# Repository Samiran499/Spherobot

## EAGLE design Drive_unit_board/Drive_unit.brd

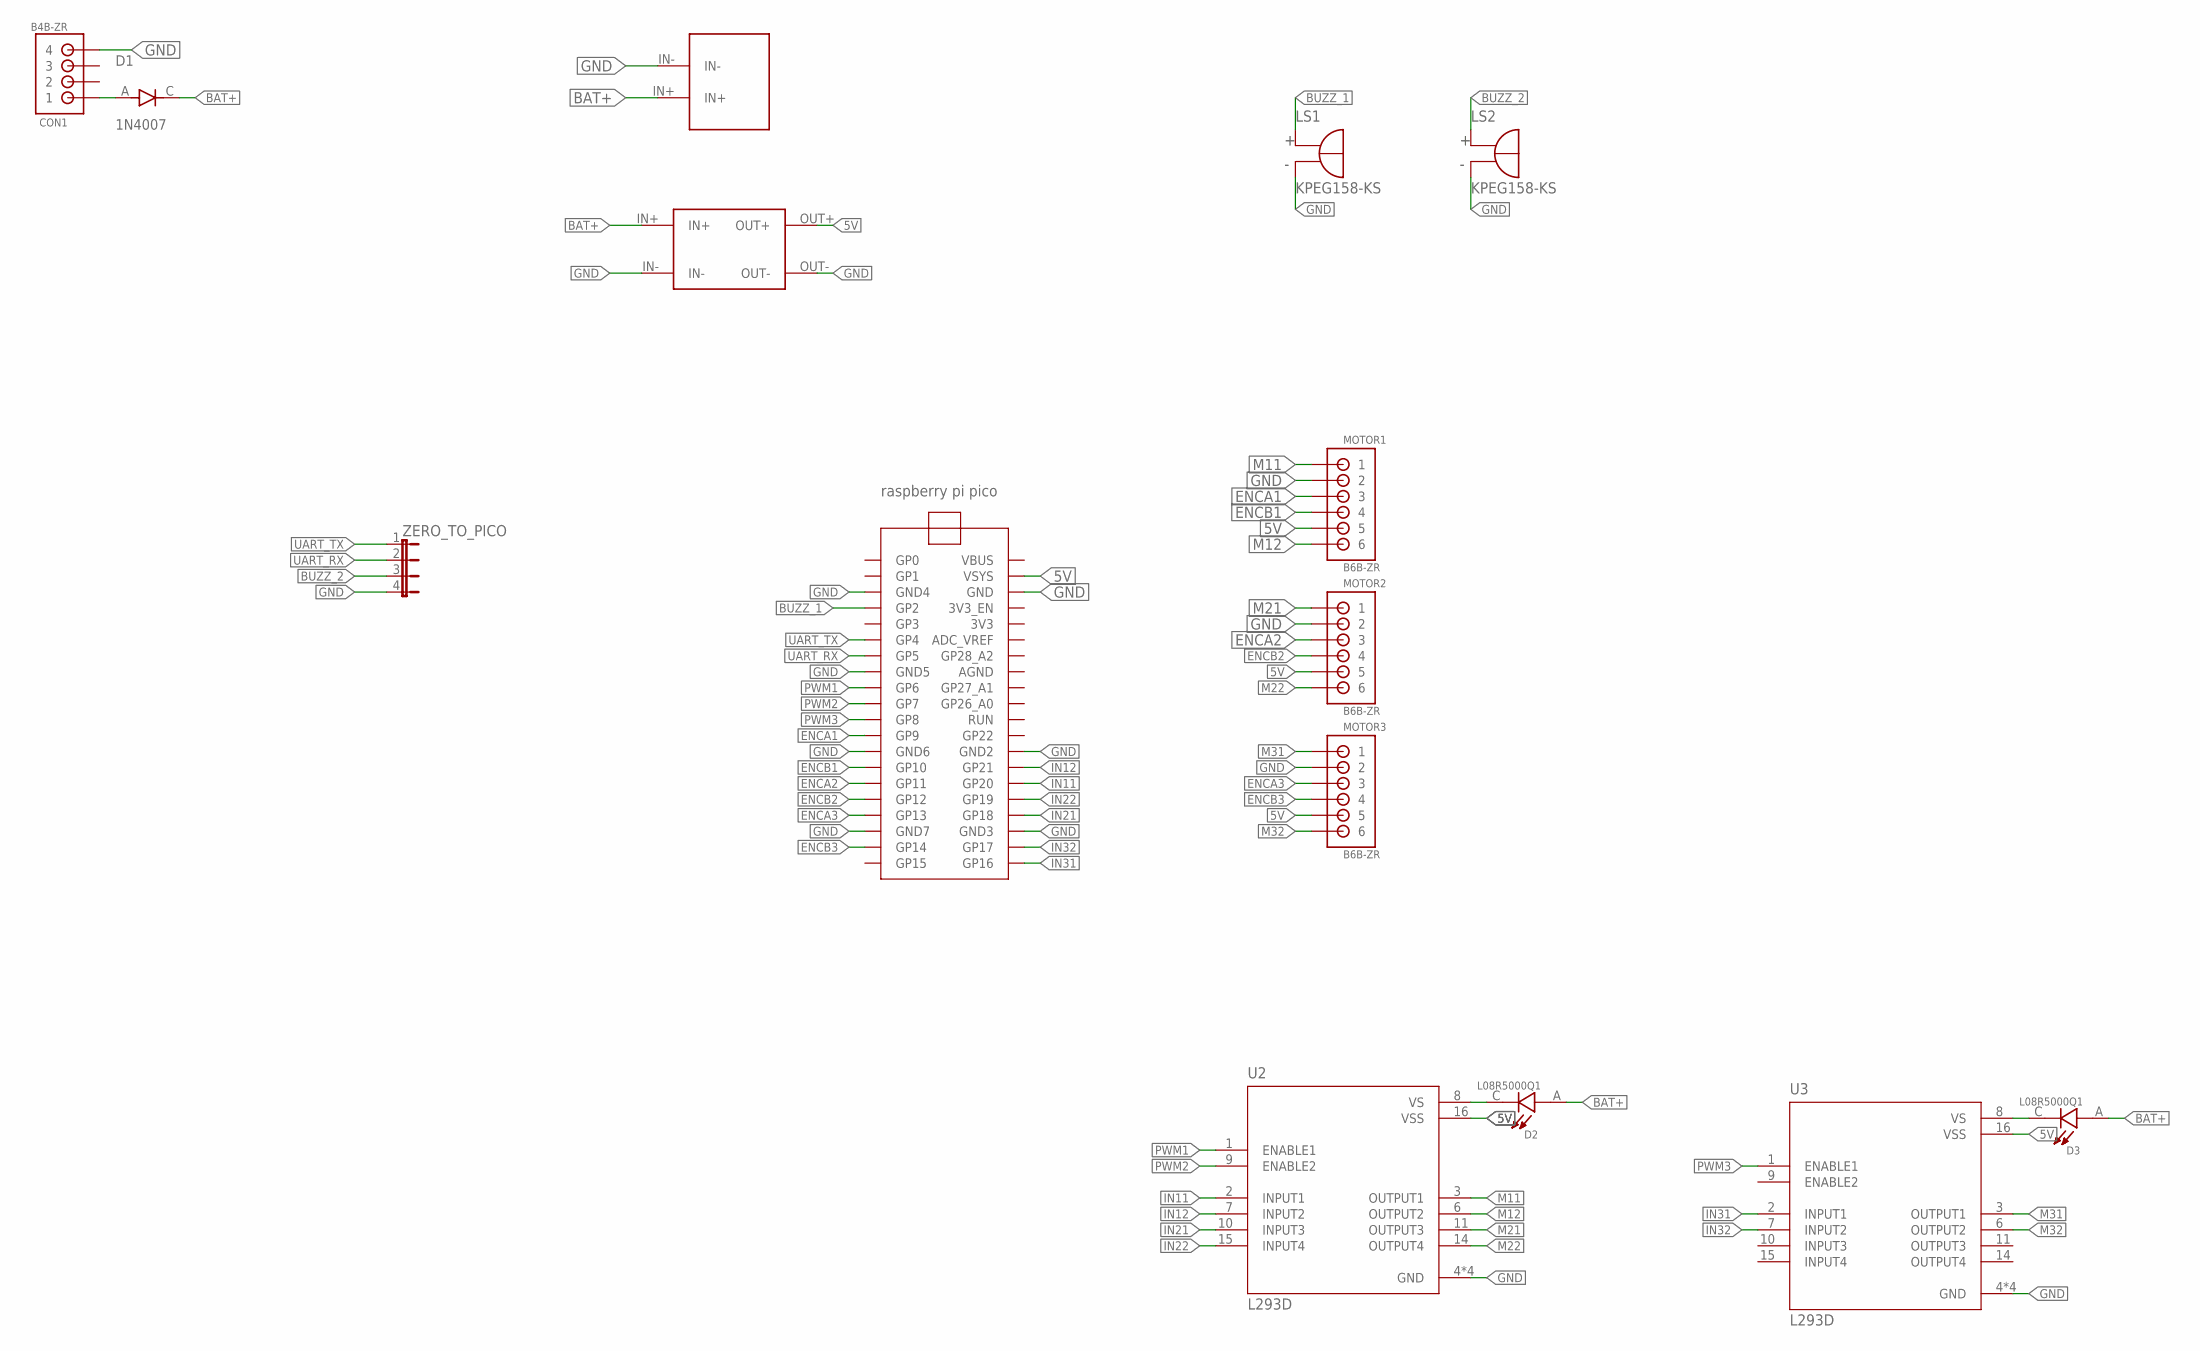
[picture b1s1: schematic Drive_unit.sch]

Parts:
CON1: B4B-ZR
D1: 1N4007; DIOAD1060W80L520D270
D2, D3: L08R5000Q1; LEDRD254W57D500H1070
LS1, LS2: KPEG158-KS; XDCR_KPEG158-KS
MOTOR1, MOTOR2, MOTOR3: B6B-ZR
U1: RASPBERRY_PI_PICO
U2, U3: L293D; DIP880W50P254L2000H510Q16
U$1: USB_BUCK
U$3: LM2596_BUCK_MODULE; LM2596_MODULE
ZERO_TO_PICO: JP4E; JP4

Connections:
5V: MOTOR1.5, MOTOR2.5, MOTOR3.5, U1.VSYS, U2.16 (VSS), U3.16 (VSS), U$3.OUT+
BAT+: D1.C, D2.A, D3.A, U$1.IN+, U$3.IN+
BUZZ_1: LS1.P (POS), U1.GP2
BUZZ_2: LS2.P (POS), ZERO_TO_PICO.3
ENCA1: MOTOR1.3, U1.GP9
ENCA2: MOTOR2.3, U1.GP11
ENCA3: MOTOR3.3, U1.GP13
ENCB1: MOTOR1.4, U1.GP10
ENCB2: MOTOR2.4, U1.GP12
ENCB3: MOTOR3.4, U1.GP14
GND: CON1.4, LS1.N (NEG), LS2.N (NEG), MOTOR1.2, MOTOR2.2, MOTOR3.2, U1.GND, U1.GND2, U1.GND3, U1.GND4, U1.GND5, U1.GND6, U1.GND7, U2.4 (GND), U2.5 (GND), U2.12 (GND), U2.13 (GND), U3.4 (GND), U3.5 (GND), U3.12 (GND), U3.13 (GND), U$1.IN-, U$3.IN-, U$3.OUT-, ZERO_TO_PICO.4
IN11: U1.GP20, U2.2 (INPUT1)
IN12: U1.GP21, U2.7 (INPUT2)
IN21: U1.GP18, U2.10 (INPUT3)
IN22: U1.GP19, U2.15 (INPUT4)
IN31: U1.GP16, U3.2 (INPUT1)
IN32: U1.GP17, U3.7 (INPUT2)
M11: MOTOR1.1, U2.3 (OUTPUT1)
M12: MOTOR1.6, U2.6 (OUTPUT2)
M21: MOTOR2.1, U2.11 (OUTPUT3)
M22: MOTOR2.6, U2.14 (OUTPUT4)
M31: MOTOR3.1, U3.3 (OUTPUT1)
M32: MOTOR3.6, U3.6 (OUTPUT2)
unnamed: CON1.1, D1.A
unnamed: D2.C, U2.8 (VS)
unnamed: D3.C, U3.8 (VS)
PWM1: U1.GP6, U2.1 (ENABLE1)
PWM2: U1.GP7, U2.9 (ENABLE2)
PWM3: U1.GP8, U3.1 (ENABLE1)
UART_RX: U1.GP5, ZERO_TO_PICO.2
UART_TX: U1.GP4, ZERO_TO_PICO.1

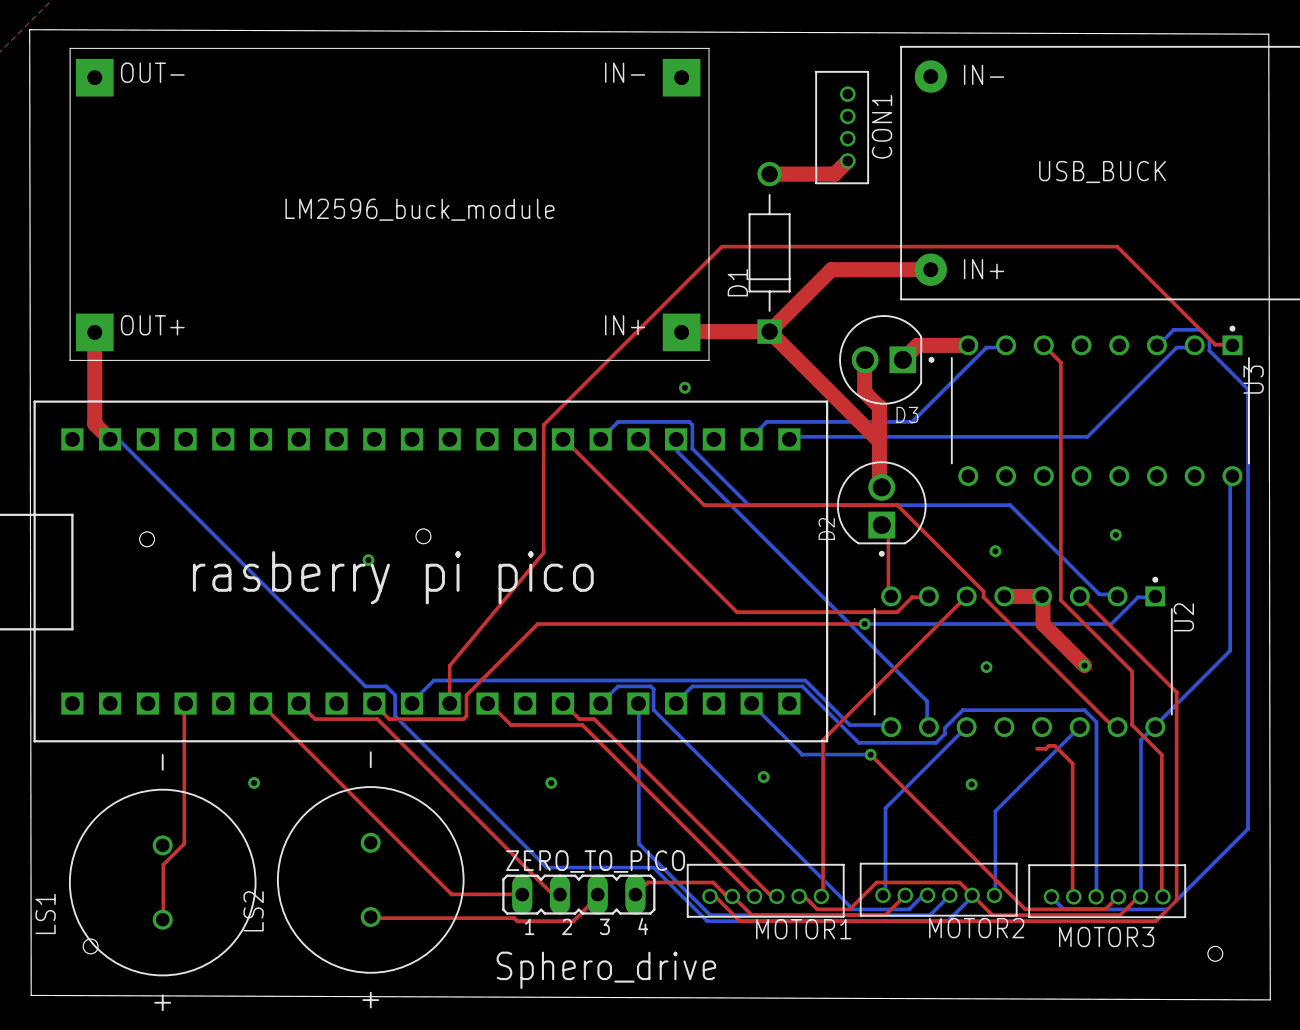
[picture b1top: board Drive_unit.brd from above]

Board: 2 copper layers, 83.5 x 65.3 mm, 15 parts (0 on the bottom side), 31 nets.

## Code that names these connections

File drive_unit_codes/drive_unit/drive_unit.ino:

#include <Arduino.h>

// Motor 1 Pins
#define ENCA1 9
#define ENCB1 10
#define PWM1 6
#define IN11 20
#define IN12 21

// Motor 2 Pins
#define ENCA2 11
#define ENCB2 12
#define PWM2 7
#define IN21 18
#define IN22 19

// Motor 3 Pins
#define ENCA3 13
#define ENCB3 14
#define PWM3 8
#define IN31 16
#define IN32 17

// Number of motors
#define NUM_MOTORS 3

// Motor control structure
typedef struct {
  // Pins
  int encA, encB, pwm, in1, in2;
  
  // Position and velocity
  volatile int pos_i;
  volatile float velocity_i;
  volatile long prevT_i;
  
  // Filtered velocity
  float vFilt;
  float vPrev;
  
  // PID control
  float eintegral;
  float eprev;
  
  // Target velocity
  float vt;
  
  // PID constants
  float kp, ki, kd;
} Motor;

// Array of motors
Motor motors[NUM_MOTORS] = {
  {ENCA1, ENCB1, PWM1, IN11, IN12, 0, 0, 0, 0, 0, 0, 0, 0, 30, 5, 0.1}, // Motor 1
  {ENCA2, ENCB2, PWM2, IN21, IN22, 0, 0, 0, 0, 0, 0, 0, 0, 30, 5, 0.1}, // Motor 2
  {ENCA3, ENCB3, PWM3, IN31, IN32, 0, 0, 0, 0, 0, 0, 0, 0, 30, 5, 0.1}  // Motor 3
};

// Timing variables
long prevT = 0;
int posPrev[NUM_MOTORS] = {0};

// UART buffer
char uartBuffer[64];
int bufferIndex = 0;

// Encoder interrupt handlers
void readEncoder1() { handleEncoderInterrupt(0); }
void readEncoder2() { handleEncoderInterrupt(1); }
void readEncoder3() { handleEncoderInterrupt(2); }

// Handle encoder interrupt for a specific motor
void handleEncoderInterrupt(int motorIndex) {
  int b = digitalRead(motors[motorIndex].encB);
  int increment = (b > 0) ? 1 : -1;
  motors[motorIndex].pos_i += increment;
  
  // Compute velocity
  long currT = micros();
  float deltaT = ((float)(currT - motors[motorIndex].prevT_i)) / 1.0e6;
  motors[motorIndex].velocity_i = increment / deltaT;
  motors[motorIndex].prevT_i = currT;
}

// Parse target speeds from UART (format "20.12,30.41,40.11")
void parseTargetSpeeds(char* buffer) {
  char* token = strtok(buffer, ",");
  for (int i = 0; i < NUM_MOTORS && token != NULL; i++) {
    float speed = atof(token);
    if (speed == 0 && token[0] != '0') { // Check for invalid conversion
      Serial.println("Error: Invalid speed value");
      return;
    }
    motors[i].vt = speed;
    token = strtok(NULL, ",");
  }
  if (token != NULL) {
    Serial.println("Error: Too many values in UART data");
  }
}

// Send actual speeds via UART1
void sendActualSpeeds() {
  String output;
  for (int i = 0; i < NUM_MOTORS; i++) {
    output += String(motors[i].vFilt, 2);
    if (i < NUM_MOTORS - 1) {
      output += ",";
    }
  }
  Serial1.println(output);
  
  // Optional: Also send to USB for debugging
  Serial.println(output);
}

// Set motor speed and direction
void setMotor(int dir, int pwmVal, int pwm, int in1, int in2) {
  analogWrite(pwm, pwmVal);
  if (dir == 1) {
    digitalWrite(in1, HIGH);
    digitalWrite(in2, LOW);
  } else if (dir == -1) {
    digitalWrite(in1, LOW);
    digitalWrite(in2, HIGH);
  } else {
    digitalWrite(in1, LOW);
    digitalWrite(in2, LOW);
  }
}

void setup() {
  // Initialize all motors
  for (int i = 0; i < NUM_MOTORS; i++) {
    pinMode(motors[i].encA, INPUT);
    pinMode(motors[i].encB, INPUT);
    pinMode(motors[i].pwm, OUTPUT);
    pinMode(motors[i].in1, OUTPUT);
    pinMode(motors[i].in2, OUTPUT);
    
    // Set PID constants (tune these for your system)
    motors[i].kp = 5.0;
    motors[i].ki = 10.0;
    motors[i].kd = 0.1;
    
    // Initialize target speed
    motors[i].vt = 0.0;
  }
  
  // Attach interrupts for each encoder
  attachInterrupt(digitalPinToInterrupt(ENCA1), readEncoder1, RISING);
  attachInterrupt(digitalPinToInterrupt(ENCA2), readEncoder2, RISING);
  attachInterrupt(digitalPinToInterrupt(ENCA3), readEncoder3, RISING);
  pinMode(25, OUTPUT);
  Serial.begin(115200);  // USB serial for debugging
  Serial1.begin(115200); // UART1 for target speed communication
  
  // while(!Serial1.available())
  // {
  //   digitalWrite(25, HIGH);
  //   delay(100);
  //   digitalWrite(25, LOW);
  //   delay(100);
  // }

  digitalWrite(25, HIGH);
}

void loop() {
  // Timing
  long currT = micros();
  float deltaT = ((float)(currT - prevT)) / 1.0e6;
  prevT = currT;

  // Process UART data if available
  while (Serial1.available()) {
    char c = Serial1.read();
    if (c == '\n') {
      uartBuffer[bufferIndex] = '\0';
      Serial.print("Received UART data: ");
      Serial.println(uartBuffer); // Debugging: Print received data
      parseTargetSpeeds(uartBuffer);
      bufferIndex = 0;
    } else if (bufferIndex < sizeof(uartBuffer) - 1) {
      uartBuffer[bufferIndex++] = c;
    } else {
      Serial.println("Error: UART buffer overflow");
      bufferIndex = 0; // Reset buffer to prevent overflow
    }
  }
  
  // Control each motor
  for (int i = 0; i < NUM_MOTORS; i++) {
    // Read position and velocity (with interrupts disabled)
    int pos = 0;
    float velocity = 0;
    noInterrupts();
    pos = motors[i].pos_i;
    velocity = motors[i].velocity_i;
    interrupts();
    
    // Compute velocity (alternative method)
    float velocityAlt = (pos - posPrev[i]) / deltaT;
    posPrev[i] = pos;
    
    // Convert count/s to RPM (adjust this based on your encoder CPR)
    float v = velocity / 1500.0*60.0;       // Method 1 (interrupt)
    float vAlt = velocityAlt / 1500.0*60.0; // Method 2 (loop timing)
    
    // Low-pass filter (25 Hz cutoff)
    motors[i].vFilt = 0.854 * motors[i].vFilt + 0.0728 * v + 0.0728 * motors[i].vPrev;
    motors[i].vPrev = v;
    
    // PID control
    float e = motors[i].vt - motors[i].vFilt;
    motors[i].eintegral += e * deltaT;
    float dedt = (e - motors[i].eprev) / deltaT;
    motors[i].eprev = e;
    
    float u = motors[i].kp * e + motors[i].ki * motors[i].eintegral + motors[i].kd * dedt;
    
    // Set motor direction and power
    int dir = (u > 0) ? 1 : -1;
    int pwr = constrain((int)fabs(u), 0, 255);
    setMotor(dir, pwr, motors[i].pwm, motors[i].in1, motors[i].in2);
  }
  
  // Send actual speeds via UART1
  // sendActualSpeeds();
  
  // Small delay to prevent USB serial flooding
  delay(1);
}

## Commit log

2025-07-11 Barebone codes added
2025-07-19 Added the Drive unit EDA files
2025-08-07 2nd iteration
2025-08-07 3rd iteration
2025-08-07 4th iteration
